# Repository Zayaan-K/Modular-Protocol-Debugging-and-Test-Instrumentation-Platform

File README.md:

# Modular-Protocol-Debugging-and-Test-Instrumentation-Platform

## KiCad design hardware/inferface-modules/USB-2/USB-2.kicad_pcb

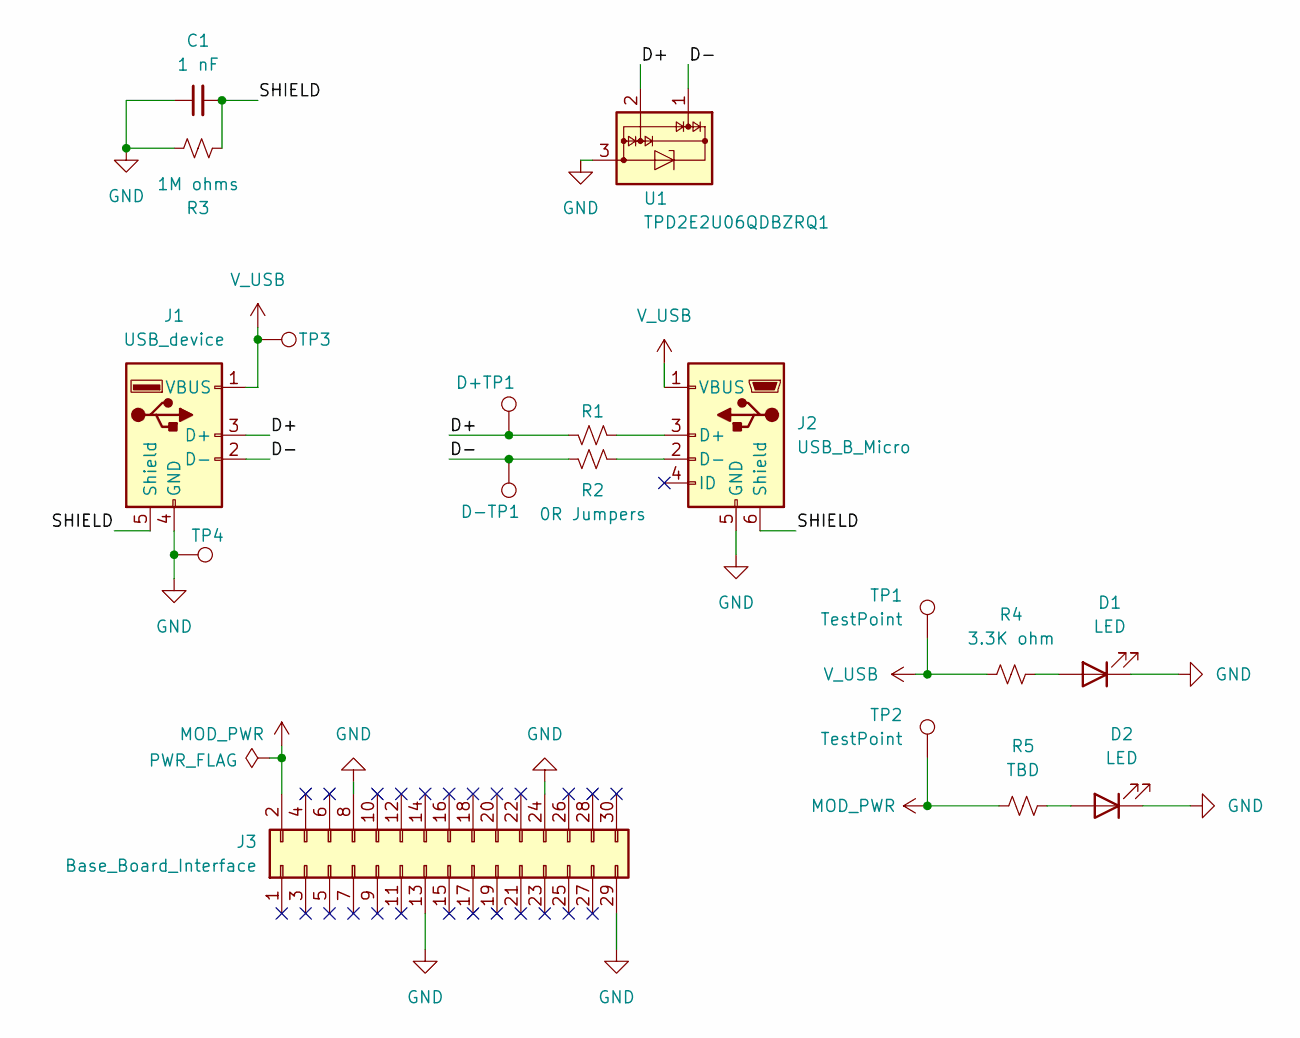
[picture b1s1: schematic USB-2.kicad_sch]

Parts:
C1: 1 nF; C_1206_3216Metric
D1, D2: LED; LED_0805_2012Metric
D+TP1: D+; TestPoint_Pad_1.0x1.0mm
D-TP1: D-; TestPoint_Pad_1.0x1.0mm
J1: USB_device; USB_A_Molex_67643_Horizontal
J2: USB_B_Micro; USB_Micro-B_Molex_47346-0001
J3: Base_Board_Interface; IDC-Header_2x15_P2.54mm_Vertical
R1: R_Small_US; R_0805_2012Metric
R2: 0R Jumpers; R_0805_2012Metric
R3: 1M ohms; R_0805_2012Metric
R4: 3.3K ohm; R_0805_2012Metric
R5: TBD; R_0805_2012Metric
TP1, TP2, TP3, TP4: TestPoint; TestPoint_Pad_1.0x1.0mm
U1: TPD2E2U06QDBZRQ1; SOT-23

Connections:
/D+: D+TP1.1, J1.3 (D+), R1.1, U1.2
/D-: D-TP1.1, J1.2 (D-), R2.1, U1.1
/SHIELD: C1.2, J1.5 (Shield), J2.6 (Shield), R3.2
GND: C1.1, D1.1 (K), D2.1 (K), J1.4 (GND), J2.5 (GND), J3.8, J3.13, J3.24, J3.29, R3.1, TP4.1, U1.3
MOD_PWR: J3.2, R5.1, TP2.1
unnamed: D1.2 (A), R4.2
unnamed: D2.2 (A), R5.2
unnamed: J2.3 (D+), R1.2
unnamed: J2.2 (D-), R2.2
V_USB: J1.1 (VBUS), J2.1 (VBUS), R4.1, TP1.1, TP3.1

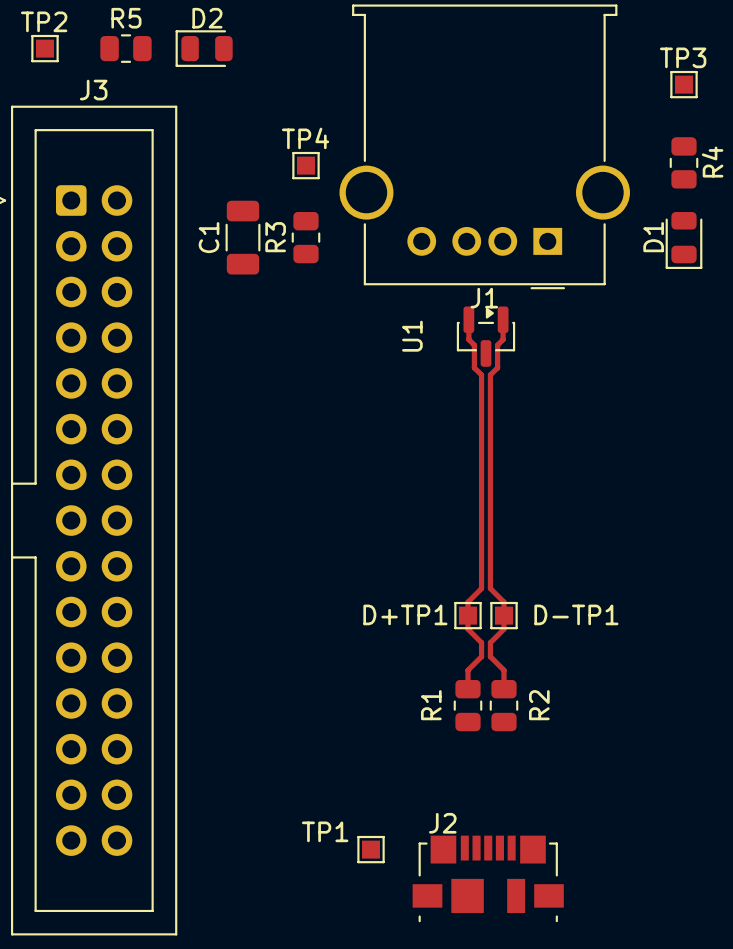
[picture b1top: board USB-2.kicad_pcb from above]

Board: 4 copper layers, 18 parts (0 on the bottom side), 10 nets.
